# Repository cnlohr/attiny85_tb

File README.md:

ATTiny85 Test Bench

I use this thing in a bunch of my videos.  It's a neat ATTiny85 carrier board that uses screw terminals.

You can see the .lst file for the parts list and if you want to buy some of the boards, you can get them from OSHPark here: https://oshpark.com/shared_projects/ZDUBhs9S

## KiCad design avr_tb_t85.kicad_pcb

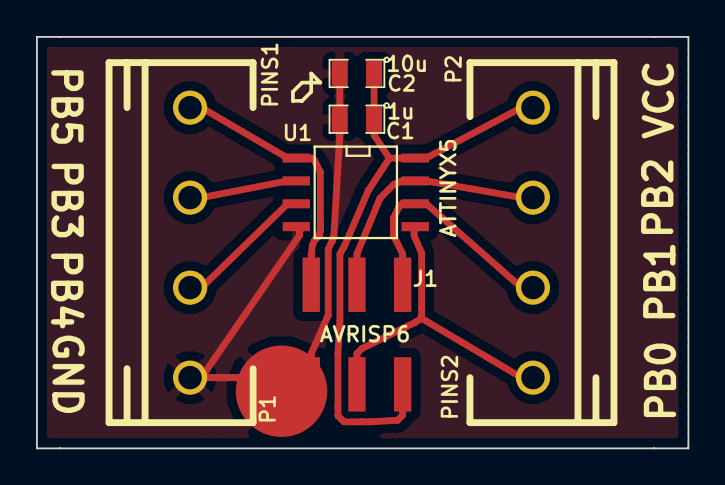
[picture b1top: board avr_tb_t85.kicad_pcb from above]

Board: 2 copper layers, 36.2 x 22.9 mm, 8 parts (1 on the bottom side), 8 nets.

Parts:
C1: 1u; SM0805
C2: 10u; SM0805
J1: AVRISP6; RIBBON6SMT
P1: PINS1; PHOENIX1935187
P2: PINS2; PHOENIX1935187
P3, P4: CONN_1; .2SMTPIN
U1: ATTINYX5; SO8WIDE

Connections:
+5V: C1.1, C2.1, J1.2, P2.4, U1.8
GND: C1.2, C2.2, J1.6, P1.4, P3.1, P4.1, U1.4
unnamed: P1.3, U1.3
unnamed: P1.2, U1.2
unnamed: J1.5, P1.1, U1.1
unnamed: J1.1, P2.2, U1.6
unnamed: J1.3, P2.3, U1.7
unnamed: J1.4, P2.1, U1.5

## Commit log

2015-03-05 add ATTiny85 test bench

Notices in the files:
avr_tb_t85.kicad_pcb:
(C) 2014 C. Lohr
